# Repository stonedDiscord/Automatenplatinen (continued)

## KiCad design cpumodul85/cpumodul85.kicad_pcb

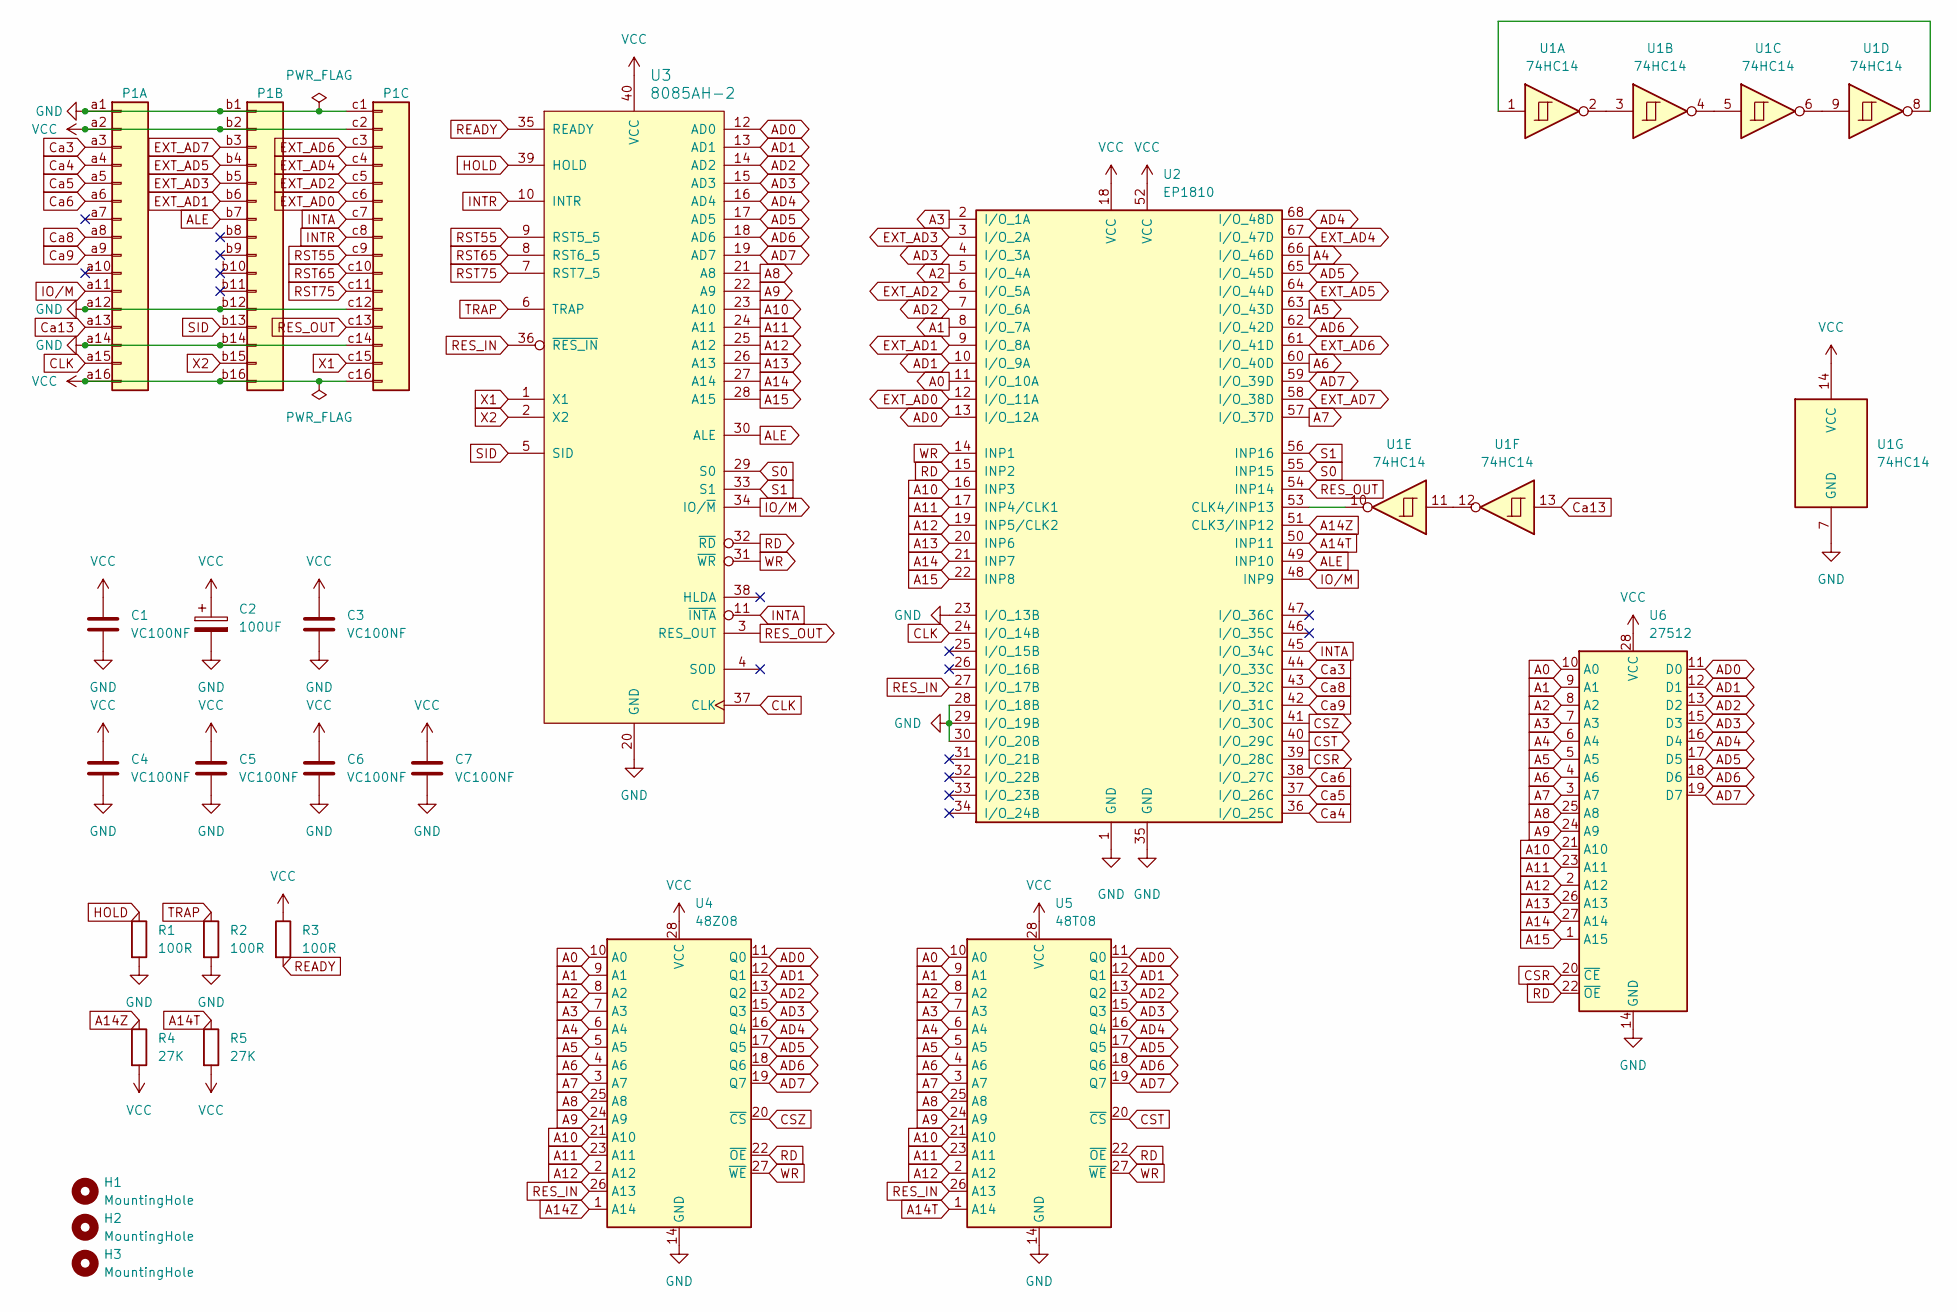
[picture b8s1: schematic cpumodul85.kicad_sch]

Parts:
C1, C3, C4, C5, C6, C7: VC100NF; C_Axial_L3.8mm_D2.6mm_P7.50mm_Horizontal
C2: 100UF; CP_Axial_L18.0mm_D6.5mm_P25.00mm_Horizontal
H1, H2, H3: MountingHole; MountingHole_5.3mm_M5
P1: DIN41612_03x16_ABC; DIN41612_C2_3x16_Female_Vertical_THT
R1, R2, R3: 100R; R_Axial_DIN0207_L6.3mm_D2.5mm_P10.16mm_Horizontal
R4, R5: 27K; R_Axial_DIN0207_L6.3mm_D2.5mm_P10.16mm_Horizontal
U1: 74HC14; DIP-14_W7.62mm
U2: EP1810; PLCC-68_THT-Socket
U3: 8085AH-2; DIP-40_W15.24mm
U4: 48Z08; DIP-28_W15.24mm
U5: 48T08; DIP-28_W15.24mm
U6: 27512; DIP-28_W15.24mm

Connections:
A0: U2.11 (I/O_10A), U4.10 (A0), U5.10 (A0), U6.10 (A0)
A1: U2.8 (I/O_7A), U4.9 (A1), U5.9 (A1), U6.9 (A1)
A2: U2.5 (I/O_4A), U4.8 (A2), U5.8 (A2), U6.8 (A2)
A3: U2.2 (I/O_1A), U4.7 (A3), U5.7 (A3), U6.7 (A3)
A4: U2.66 (I/O_46D), U4.6 (A4), U5.6 (A4), U6.6 (A4)
A5: U2.63 (I/O_43D), U4.5 (A5), U5.5 (A5), U6.5 (A5)
A6: U2.60 (I/O_40D), U4.4 (A6), U5.4 (A6), U6.4 (A6)
A7: U2.57 (I/O_37D), U4.3 (A7), U5.3 (A7), U6.3 (A7)
A8: U3.21 (A8), U4.25 (A8), U5.25 (A8), U6.25 (A8)
A9: U3.22 (A9), U4.24 (A9), U5.24 (A9), U6.24 (A9)
A10: U2.16 (INP3), U3.23 (A10), U4.21 (A10), U5.21 (A10), U6.21 (A10)
A11: U2.17 (INP4/CLK1), U3.24 (A11), U4.23 (A11), U5.23 (A11), U6.23 (A11)
A12: U2.19 (INP5/CLK2), U3.25 (A12), U4.2 (A12), U5.2 (A12), U6.2 (A12)
A13: U2.20 (INP6), U3.26 (A13), U6.26 (A13)
A14: U2.21 (INP7), U3.27 (A14), U6.27 (A14)
A14T: R5.1, U2.50 (INP11), U5.1 (A14)
A14Z: R4.1, U2.51 (CLK3/INP12), U4.1 (A14)
A15: U2.22 (INP8), U3.28 (A15), U6.1 (A15)
AD0: U2.13 (I/O_12A), U3.12 (AD0), U4.11 (Q0), U5.11 (Q0), U6.11 (D0)
AD1: U2.10 (I/O_9A), U3.13 (AD1), U4.12 (Q1), U5.12 (Q1), U6.12 (D1)
AD2: U2.7 (I/O_6A), U3.14 (AD2), U4.13 (Q2), U5.13 (Q2), U6.13 (D2)
AD3: U2.4 (I/O_3A), U3.15 (AD3), U4.15 (Q3), U5.15 (Q3), U6.15 (D3)
AD4: U2.68 (I/O_48D), U3.16 (AD4), U4.16 (Q4), U5.16 (Q4), U6.16 (D4)
AD5: U2.65 (I/O_45D), U3.17 (AD5), U4.17 (Q5), U5.17 (Q5), U6.17 (D5)
AD6: U2.62 (I/O_42D), U3.18 (AD6), U4.18 (Q6), U5.18 (Q6), U6.18 (D6)
AD7: U2.59 (I/O_39D), U3.19 (AD7), U4.19 (Q7), U5.19 (Q7), U6.19 (D7)
ALE: P1.b7, U2.49 (INP10), U3.30 (ALE)
CLK: P1.a15, U2.24 (I/O_14B), U3.37 (CLK)
CSR: U2.39 (I/O_28C), U6.20 (~CE)
CST: U2.40 (I/O_29C), U5.20 (~CS)
CSZ: U2.41 (I/O_30C), U4.20 (~CS)
Ca3: P1.a3, U2.44 (I/O_33C)
Ca4: P1.a4, U2.36 (I/O_25C)
Ca5: P1.a5, U2.37 (I/O_26C)
Ca6: P1.a6, U2.38 (I/O_27C)
Ca8: P1.a8, U2.43 (I/O_32C)
Ca9: P1.a9, U2.42 (I/O_31C)
Ca13: P1.a13, U1.13
EXT_AD0: P1.c6, U2.12 (I/O_11A)
EXT_AD1: P1.b6, U2.9 (I/O_8A)
EXT_AD2: P1.c5, U2.6 (I/O_5A)
EXT_AD3: P1.b5, U2.3 (I/O_2A)
EXT_AD4: P1.c4, U2.67 (I/O_47D)
EXT_AD5: P1.b4, U2.64 (I/O_44D)
EXT_AD6: P1.c3, U2.61 (I/O_41D)
EXT_AD7: P1.b3, U2.58 (I/O_38D)
GND: C1.2, C2.2, C3.2, C4.2, C5.2, C6.2, C7.2, P1.a1, P1.a12, P1.a14, P1.b1, P1.b12, P1.b14, P1.c1, P1.c12, P1.c14, R1.2, R2.2, U1.7 (GND), U2.1 (GND), U2.23 (I/O_13B), U2.28 (I/O_18B), U2.29 (I/O_19B), U2.30 (I/O_20B), U2.35 (GND), U3.20 (GND), U4.14 (GND), U5.14 (GND), U6.14 (GND)
HOLD: R1.1, U3.39 (HOLD)
INTA: P1.c7, U2.45 (I/O_34C), U3.11 (~INTA)
INTR: P1.c8, U3.10 (INTR)
IO/M: P1.a11, U2.48 (INP9), U3.34 (IO/~M)
unnamed: U1.1, U1.8
unnamed: U1.2, U1.3
unnamed: U1.4, U1.5
unnamed: U1.6, U1.9
unnamed: U1.11, U1.12
unnamed: U1.10, U2.53 (CLK4/INP13)
RD: U2.15 (INP2), U3.32 (~RD), U4.22 (~OE), U5.22 (~OE), U6.22 (~OE)
READY: R3.2, U3.35 (READY)
RES_IN: U2.27 (I/O_17B), U3.36 (~RES_IN), U4.26 (A13), U5.26 (A13)
RES_OUT: P1.c13, U2.54 (INP14), U3.3 (RES_OUT)
RST55: P1.c9, U3.9 (RST5_5)
RST65: P1.c10, U3.8 (RST6_5)
RST75: P1.c11, U3.7 (RST7_5)
S0: U2.55 (INP15), U3.29 (S0)
S1: U2.56 (INP16), U3.33 (S1)
SID: P1.b13, U3.5 (SID)
TRAP: R2.1, U3.6 (TRAP)
VCC: C1.1, C2.1, C3.1, C4.1, C5.1, C6.1, C7.1, P1.a2, P1.a16, P1.b2, P1.b16, P1.c2, P1.c16, R3.1, R4.2, R5.2, U1.14 (VCC), U2.18 (VCC), U2.52 (VCC), U3.40 (VCC), U4.28 (VCC), U5.28 (VCC), U6.28 (VCC)
WR: U2.14 (INP1), U3.31 (~WR), U4.27 (~WE), U5.27 (~WE)
X1: P1.c15, U3.1 (X1)
X2: P1.b15, U3.2 (X2)

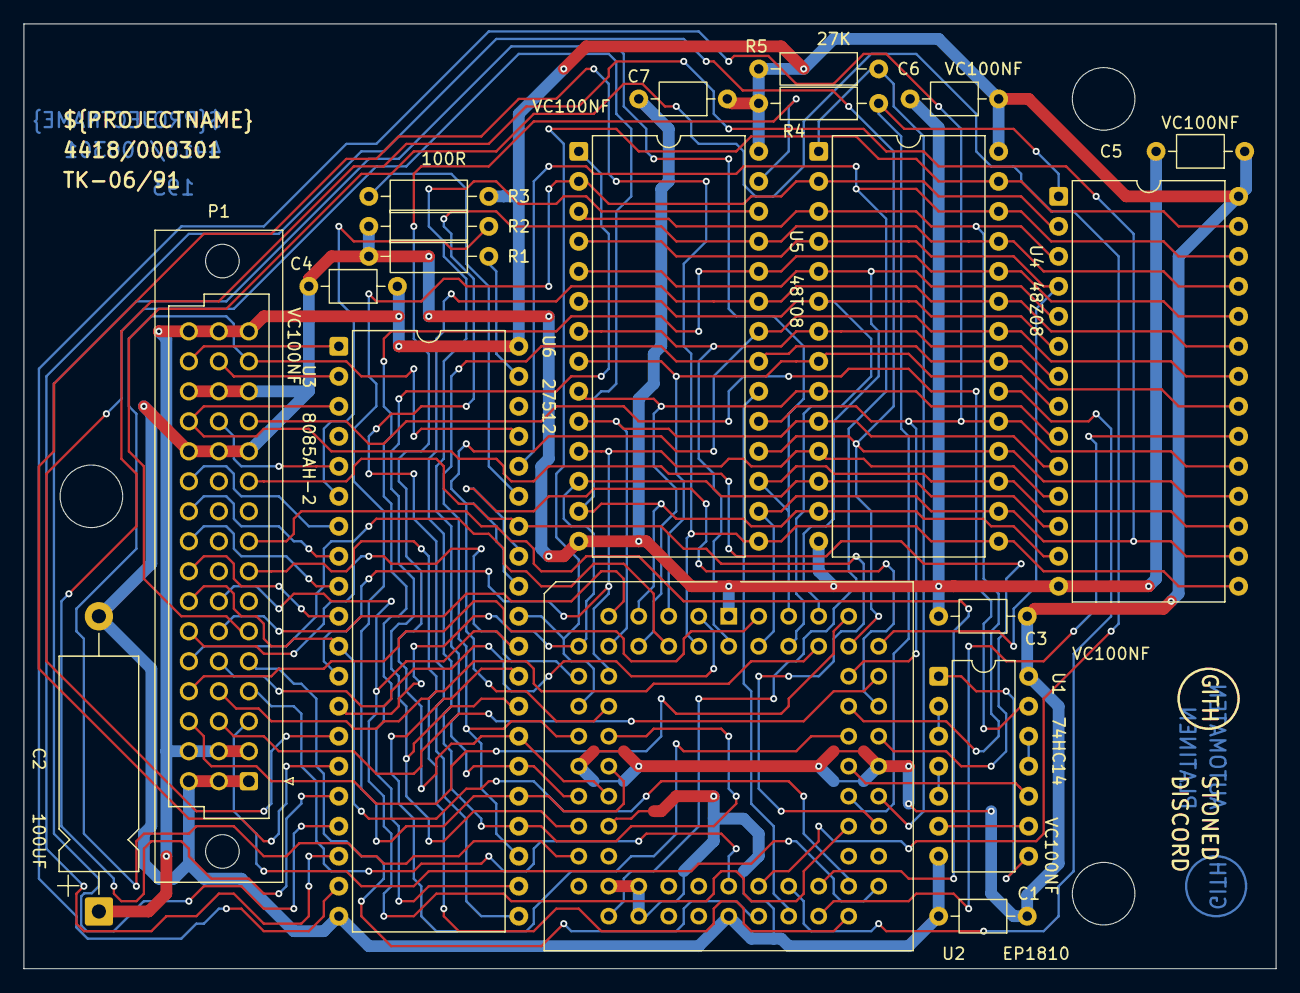
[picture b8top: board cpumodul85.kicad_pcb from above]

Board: 2 copper layers, 106.0 x 80.0 mm, 22 parts (0 on the bottom side), 72 nets.
